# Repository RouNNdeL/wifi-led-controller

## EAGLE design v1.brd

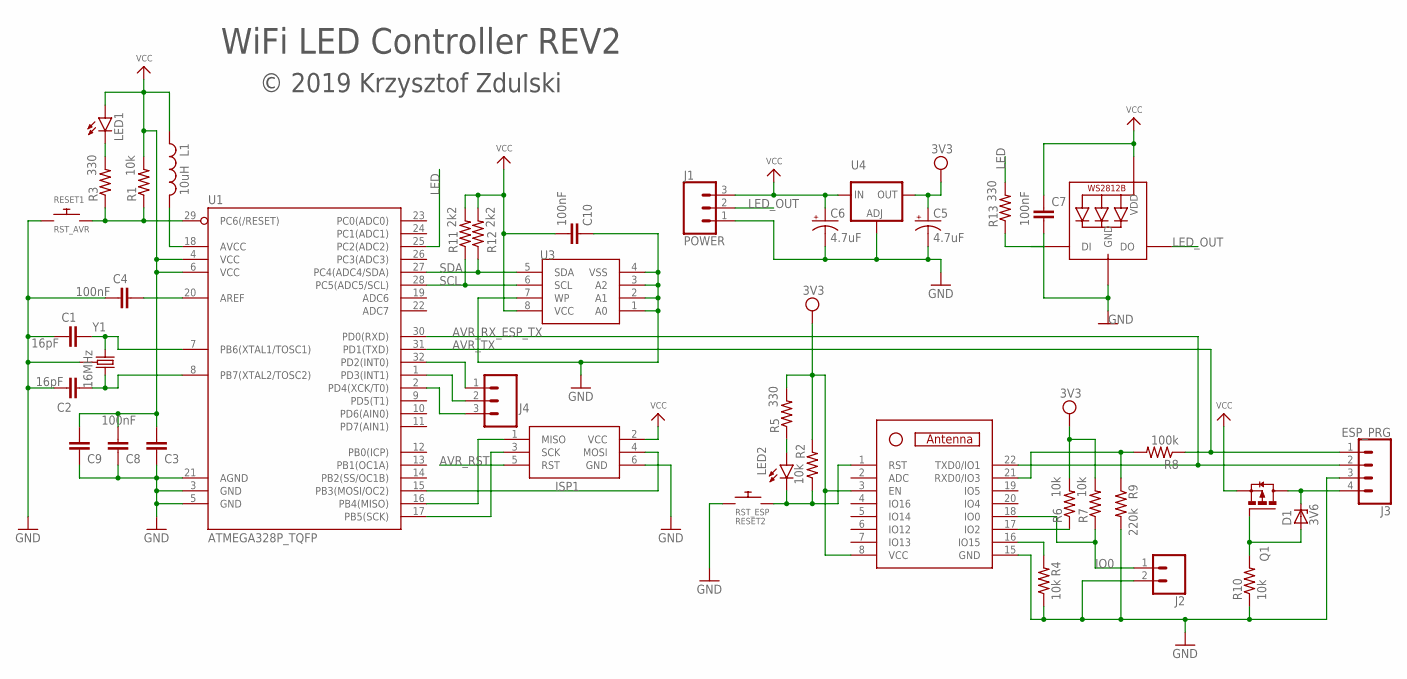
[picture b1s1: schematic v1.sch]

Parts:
C1, C2: 16pF; C0603K
C3, C4, C7, C8, C9, C10: 100nF; C0603
C5, C6: 4.7uF; 153CLV-0405
D1: 3V6; SOD123
D2: WS2812B
ISP1: AVRISP-6; AVRISP
J1: POWER; MX-22-05-3031
J2: CONN_02; 1X02
J3: ESP_PRG; 1X04
J4: CONN_03; 1X03
L1: 10uH; L2012C
LED1, LED2: LEDCHIP-LED0603; CHIP-LED0603
Q1: FDN360P; SUPER-SOT3
R1, R2, R10: 10k; R0402
R3, R5, R13: 330; R0603
R4, R6, R7: 10k; R0603
R8: 100k; R0603
R9: 220k; R0603
R11, R12: 2k2; R0603
RESET1: RST_AVR; TACTILE_SWITCH_SMD_6.2MM_TALL
RESET2: RST_ESP; TACTILE_SWITCH_SMD_6.2MM_TALL
U1: ATMEGA328P_TQFP; TQFP32-08
U2: ESP-07
U3: EEPROM-I2CTSSOP8; TSSOP8
U4: LD117AS12TR; SOT223
Y1: 16MHz; CRYSTAL-SMD-3.2X2.5MM

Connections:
3V3: C5.+, R2.2, R5.2, R6.2, R7.2, U2.3 (EN), U2.8 (VCC), U4.4 (OUT)
AREF: C4.2, U1.20 (AREF)
AVCC: L1.2, U1.18 (AVCC)
AVR_RST: ISP1.5 (RST), R1.1, R3.1, RESET1.B1, RESET1.B2, U1.29 (PC6(/RESET))
AVR_RST_LED: LED1.C, R3.2
AVR_RX_ESP_TX: J3.2, U1.30 (PD0(RXD)), U2.22 (TXD0/IO1)
AVR_TX: J3.1, R8.1, U1.31 (PD1(TXD))
ESP_RST: LED2.C, R2.1, RESET2.B1, RESET2.B2, U2.1 (RST)
ESP_RX: R8.2, R9.1, U2.21 (RXD0/IO3)
GND: C1.2, C2.2, C3.2, C4.1, C5.-, C6.-, C7.2, C8.2, C9.2, C10.2, D2.3-GND (GND), ISP1.6 (GND), J1.1, J2.2, J3.3, R4.1, R9.2, R10.1, RESET1.A1, RESET1.A2, RESET2.A1, RESET2.A2, U1.3 (GND), U1.5 (GND), U1.21 (AGND), U2.15 (GND), U3.1 (A0), U3.2 (A1), U3.3 (A2), U3.4 (VSS), U3.7 (WP), U4.1 (ADJ), Y1.2 (3), Y1.4 (3)
IO0: J2.1, R7.1, U2.18 (IO0)
IO2: R6.1, U2.17 (IO2)
IO15: R4.2, U2.16 (IO15)
LED: R13.2, U1.25 (PC2(ADC2))
LED_OUT: D2.2-DOUT (DO), J1.2
MISO: ISP1.1 (MISO), U1.16 (PB4(MISO))
MOSI: ISP1.4 (MOSI), U1.15 (PB3(MOSI/OC2))
N: D2.4-DIN (DI), R13.1
unnamed: LED2.A, R5.1
unnamed: D1.A, Q1.1 (G), R10.2
PD2: J4.1, U1.32 (PD2(INT0))
PD3: J4.2, U1.1 (PD3(INT1))
PD4: J4.3, U1.2 (PD4(XCK/T0))
SCK: ISP1.3 (SCK), U1.17 (PB5(SCK))
SCL: R11.1, U1.28 (PC5(ADC5/SCL)), U3.6 (SCL)
SDA: R12.1, U1.27 (PC4(ADC4/SDA)), U3.5 (SDA)
VCC: C3.1, C6.+, C7.1, C8.1, C9.1, C10.1, D2.1-VDD (VDD), ISP1.2 (VCC), J1.3, L1.1, LED1.A, Q1.2 (S), R1.2, R11.2, R12.2, U1.4 (VCC), U1.6 (VCC), U3.8 (VCC), U4.3 (IN)
VCC_PRG: D1.C, J3.4, Q1.3 (D)
XTAL1: C1.1, U1.7 (PB6(XTAL1/TOSC1)), Y1.1
XTAL2: C2.1, U1.8 (PB7(XTAL2/TOSC2)), Y1.3 (2)

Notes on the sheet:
WiFi LED Controller REV2
© 2019 Krzysztof Zdulski

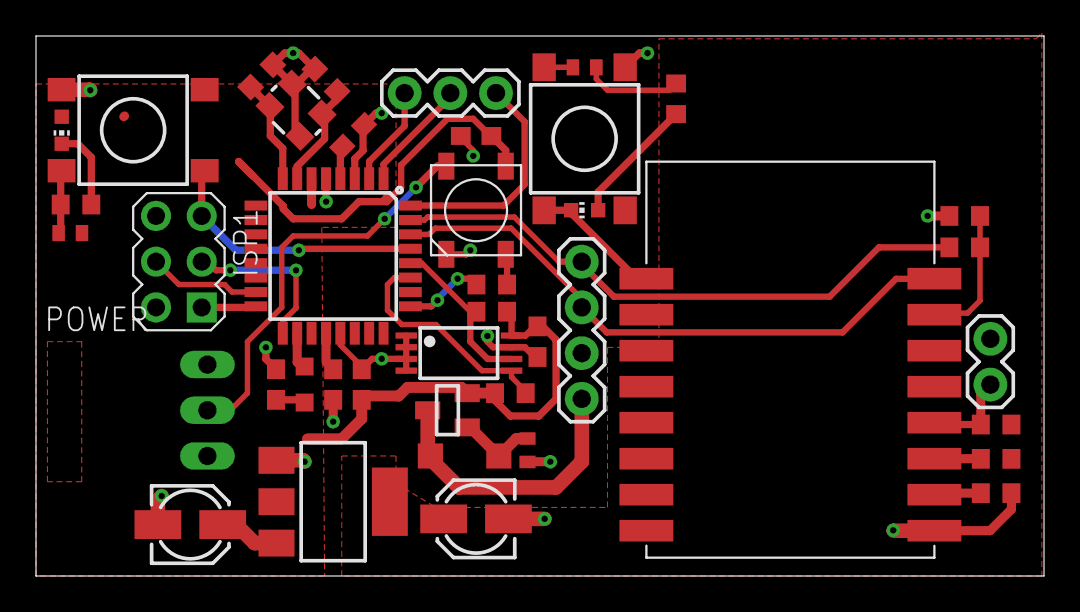
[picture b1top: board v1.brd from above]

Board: 2 copper layers, 56.0 x 30.0 mm, 41 parts (0 on the bottom side), 30 nets.

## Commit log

2019-08-02 Create LICENSE

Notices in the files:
parts and their libraries:
SparkFun-IC-Microcontroller: Licensing: Creative Commons ShareAlike 4.0 International - https://creativecommons.org/licenses/by-sa/4.0
